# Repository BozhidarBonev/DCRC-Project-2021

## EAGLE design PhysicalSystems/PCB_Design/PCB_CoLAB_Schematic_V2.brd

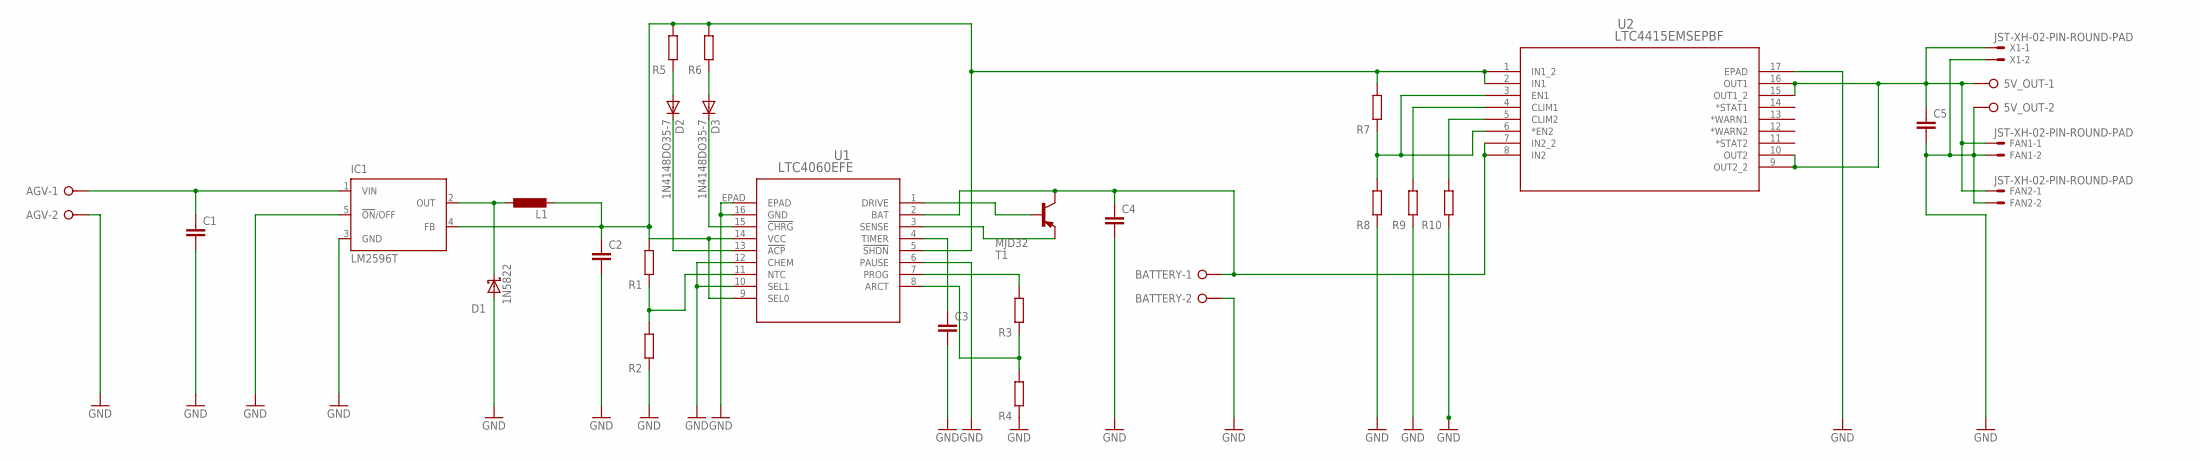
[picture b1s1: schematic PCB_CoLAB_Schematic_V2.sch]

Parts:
5V_OUT: W237-02P; W237-132
AGV: W237-02P; W237-132
BATTERY: W237-02P; W237-132
C1, C2, C3, C4, C5: C-EU025-024X044; C025-024X044
D1: 1N5822; DIOAD2120W130L950D530P
D2, D3: 1N4148DO35-7; DO35-7
FAN1, FAN2: JST-XH-02-PIN-ROUND-PAD; JST-XH-02-PACKAGE-ROUND-PAD
IC1: LM2596T; T05D
L1: L-EU0204/7; 0204/7
R1, R2, R3, R4, R5, R6, R7, R8, R9, R10: R0204/7; 0204/7
T1: MJD32; DPAK
U1: LTC4060EFE; TSSOP-16_FE/BC_LIT
U2: LTC4415EMSEPBF; MSOP-16_MSE
X1: JST-XH-02-PIN-ROUND-PAD; JST-XH-02-PACKAGE-ROUND-PAD

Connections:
GND: 5V_OUT.2, AGV.2, BATTERY.2, C1.2, C2.2, C3.2, C4.2, C5.2, D1.A, FAN1.2, FAN2.2, IC1.3 (GND), IC1.5 (!ON!/OFF), R2.1, R4.1, R8.1, R9.1, R10.1, U1.6 (PAUSE), U1.10 (SEL1), U1.12 (CHEM), U1.16 (GND), U1.EPAD, U2.17 (EPAD), X1.2
unnamed: R3.2, U1.7 (PROG)
unnamed: AGV.1, C1.1, IC1.1 (VIN)
unnamed: D1.C, IC1.2 (OUT), L1.1
unnamed: R1.1, R2.2, U1.11 (NTC)
unnamed: R7.1, R8.2, U2.3 (EN1), U2.6 (*EN2)
unnamed: R3.1, R4.2, U1.8 (ARCT)
unnamed: T1.3 (E), U1.3 (SENSE)
unnamed: T1.1 (B), U1.1 (DRIVE)
unnamed: C2.1, IC1.4 (FB), L1.2, R1.2, R5.2, R6.2, R7.2, U1.5 (!SHDN), U1.9 (SEL0), U1.14 (VCC), U2.1 (IN1_2), U2.2 (IN1)
unnamed: C3.1, U1.4 (TIMER)
unnamed: D2.A, R5.1
unnamed: D2.C, U1.13 (!ACP)
unnamed: D3.C, U1.15 (!CHRG)
unnamed: D3.A, R6.1
unnamed: BATTERY.1, C4.1, T1.4 (C), U1.2 (BAT), U2.7 (IN2_2), U2.8 (IN2)
unnamed: R9.2, U2.4 (CLIM1)
unnamed: R10.2, U2.5 (CLIM2)
unnamed: 5V_OUT.1, C5.1, FAN1.1, FAN2.1, U2.9 (OUT2_2), U2.10 (OUT2), U2.15 (OUT1_2), U2.16 (OUT1), X1.1

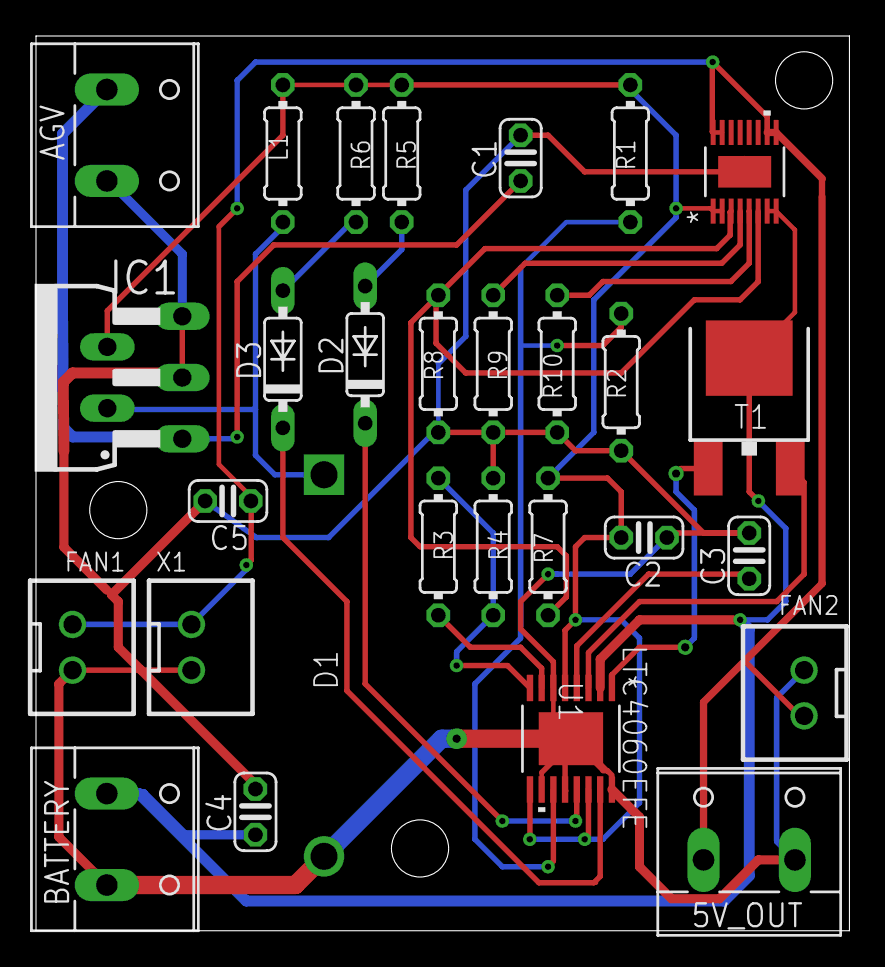
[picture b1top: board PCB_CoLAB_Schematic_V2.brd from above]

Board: 2 copper layers, 45.2 x 49.7 mm, 29 parts (1 on the bottom side), 19 nets.
